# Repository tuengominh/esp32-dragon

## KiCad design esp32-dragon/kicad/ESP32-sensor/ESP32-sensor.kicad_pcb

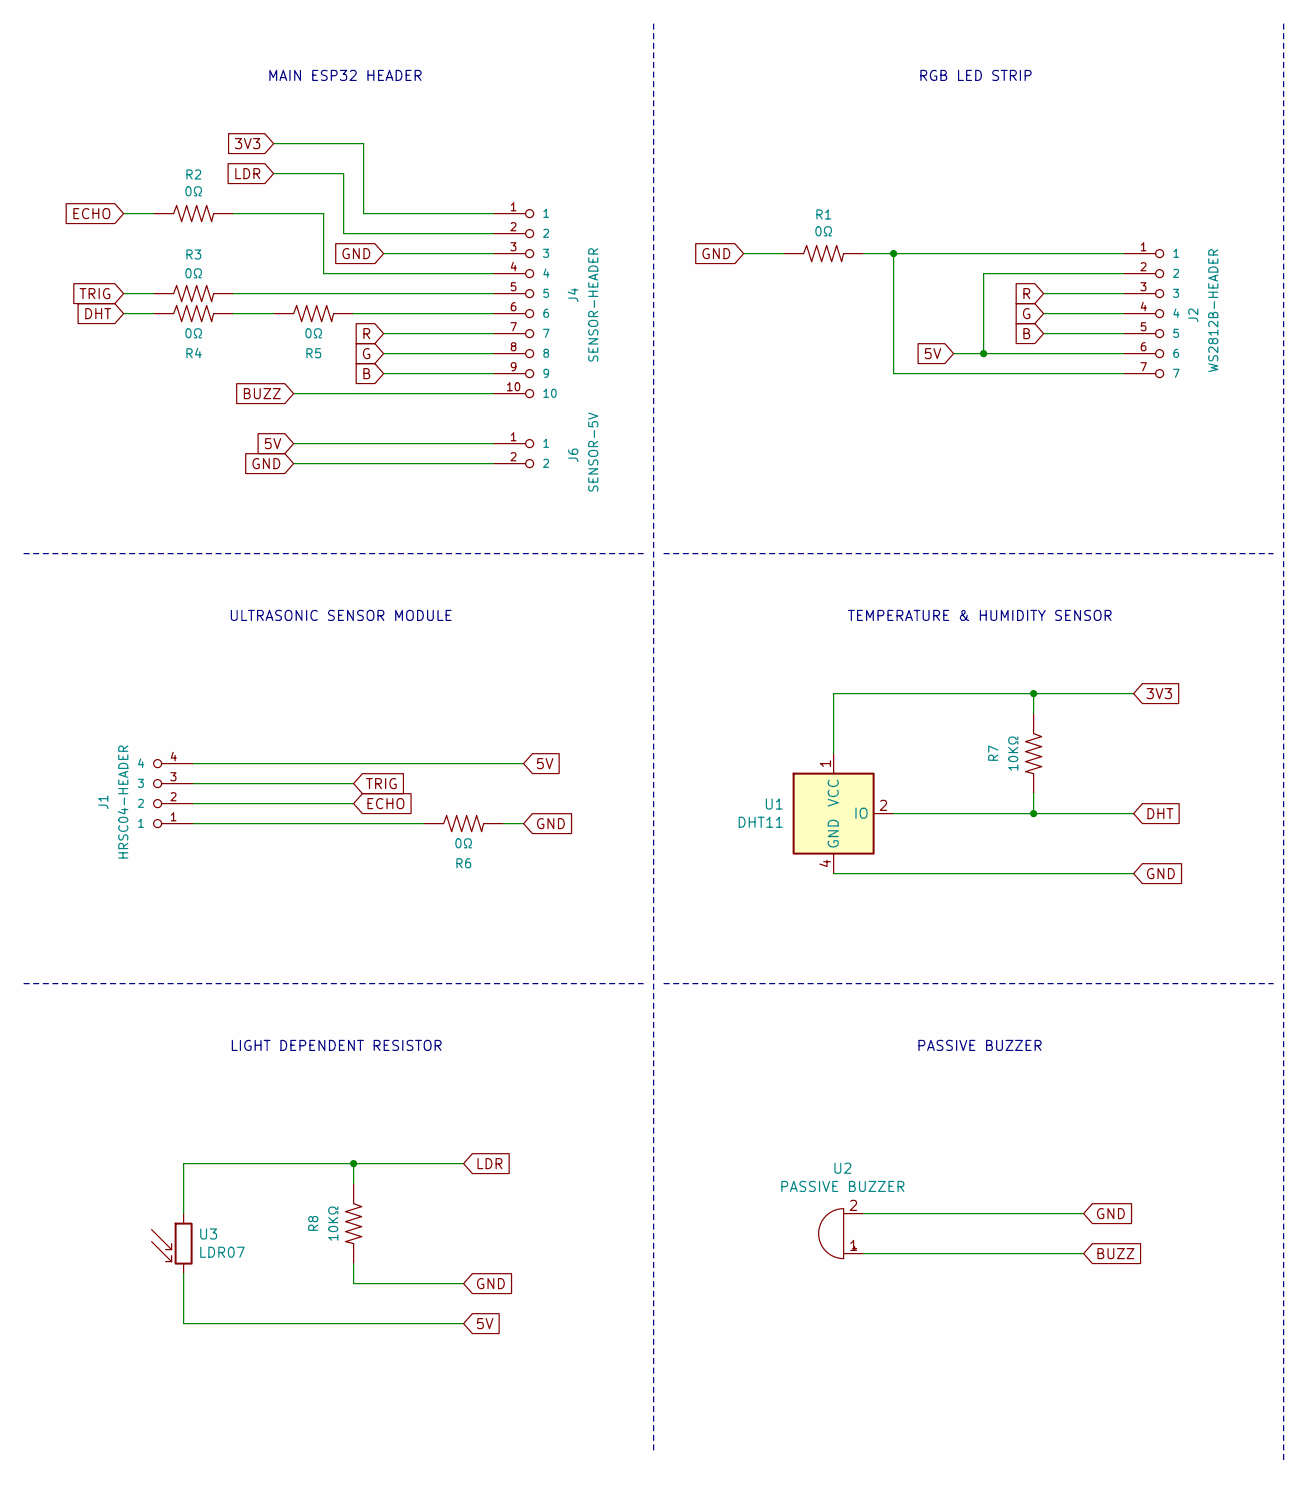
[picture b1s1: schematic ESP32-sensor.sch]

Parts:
J1: HRSC04-HEADER; fab-1X04
J2: WS2812B-HEADER; fab-1X07
J4: SENSOR-HEADER; fab-1X10
J6: SENSOR-5V; fab-1X02
R1, R2, R3, R4, R5, R6: 0Ω; fab-R1206FAB
R7, R8: 10KΩ; fab-R1206FAB
U1: DHT11; Aosong_DHT11_5.5x12.0_P2.54mm
U2: PASSIVE BUZZER; Buzzer_12x9.5RM7.6
U3: LDR07; R_LDR_5.1x4.3mm_P3.4mm_Vertical

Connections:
3V3: J4.1, R7.1, U1.1 (VCC)
5V: J1.4, J2.2, J2.6, J6.1, U3.2
B: J2.5, J4.9
BUZZ: J4.10, U2.1 (-)
DHT: R4.1, R7.2, U1.2 (IO)
ECHO: J1.2, R2.1
G: J2.4, J4.8
GND: J4.3, J6.2, R1.1, R6.2, R8.2, U1.4 (GND), U2.2 (+)
LDR: J4.2, R8.1, U3.1
unnamed: J1.1, R6.1
unnamed: J2.1, J2.7, R1.2
unnamed: J4.4, R2.2
unnamed: J4.5, R3.2
unnamed: J4.6, R5.2
unnamed: R4.2, R5.1
R: J2.3, J4.7
TRIG: J1.3, R3.1

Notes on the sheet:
MAIN ESP32 HEADER
RGB LED STRIP
ULTRASONIC SENSOR MODULE
TEMPERATURE & HUMIDITY SENSOR
PASSIVE BUZZER
LIGHT DEPENDENT RESISTOR

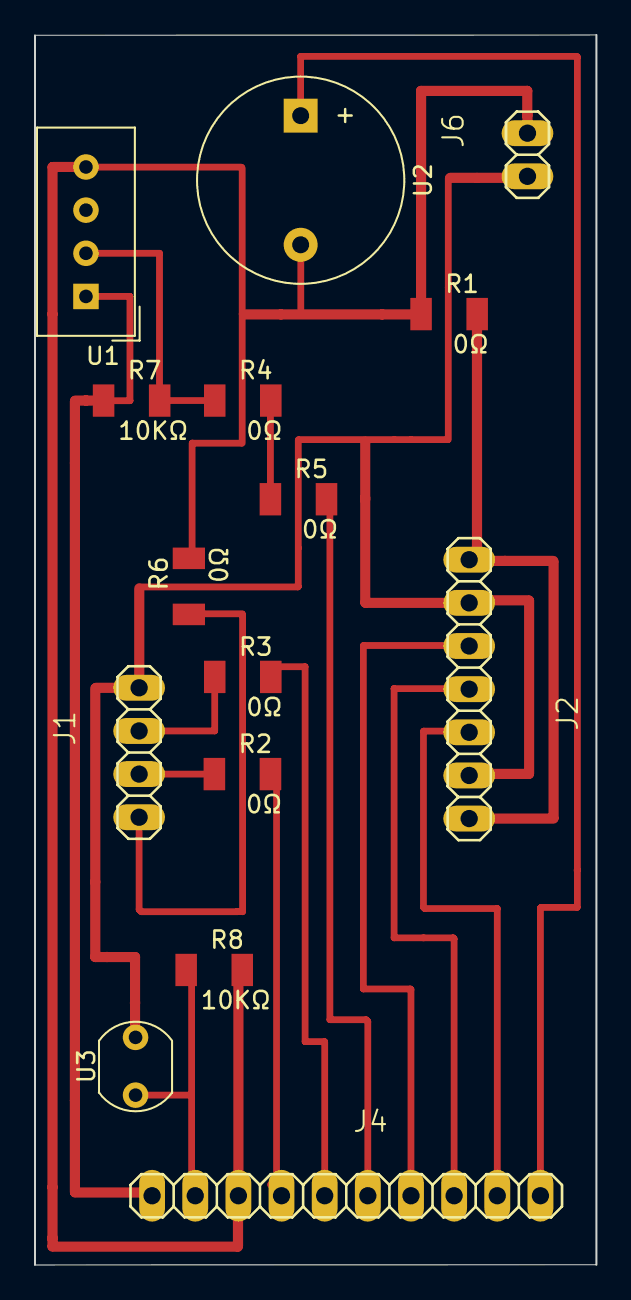
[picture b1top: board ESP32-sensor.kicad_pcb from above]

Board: 2 copper layers, 33.1 x 72.4 mm, 15 parts (0 on the bottom side), 17 nets.

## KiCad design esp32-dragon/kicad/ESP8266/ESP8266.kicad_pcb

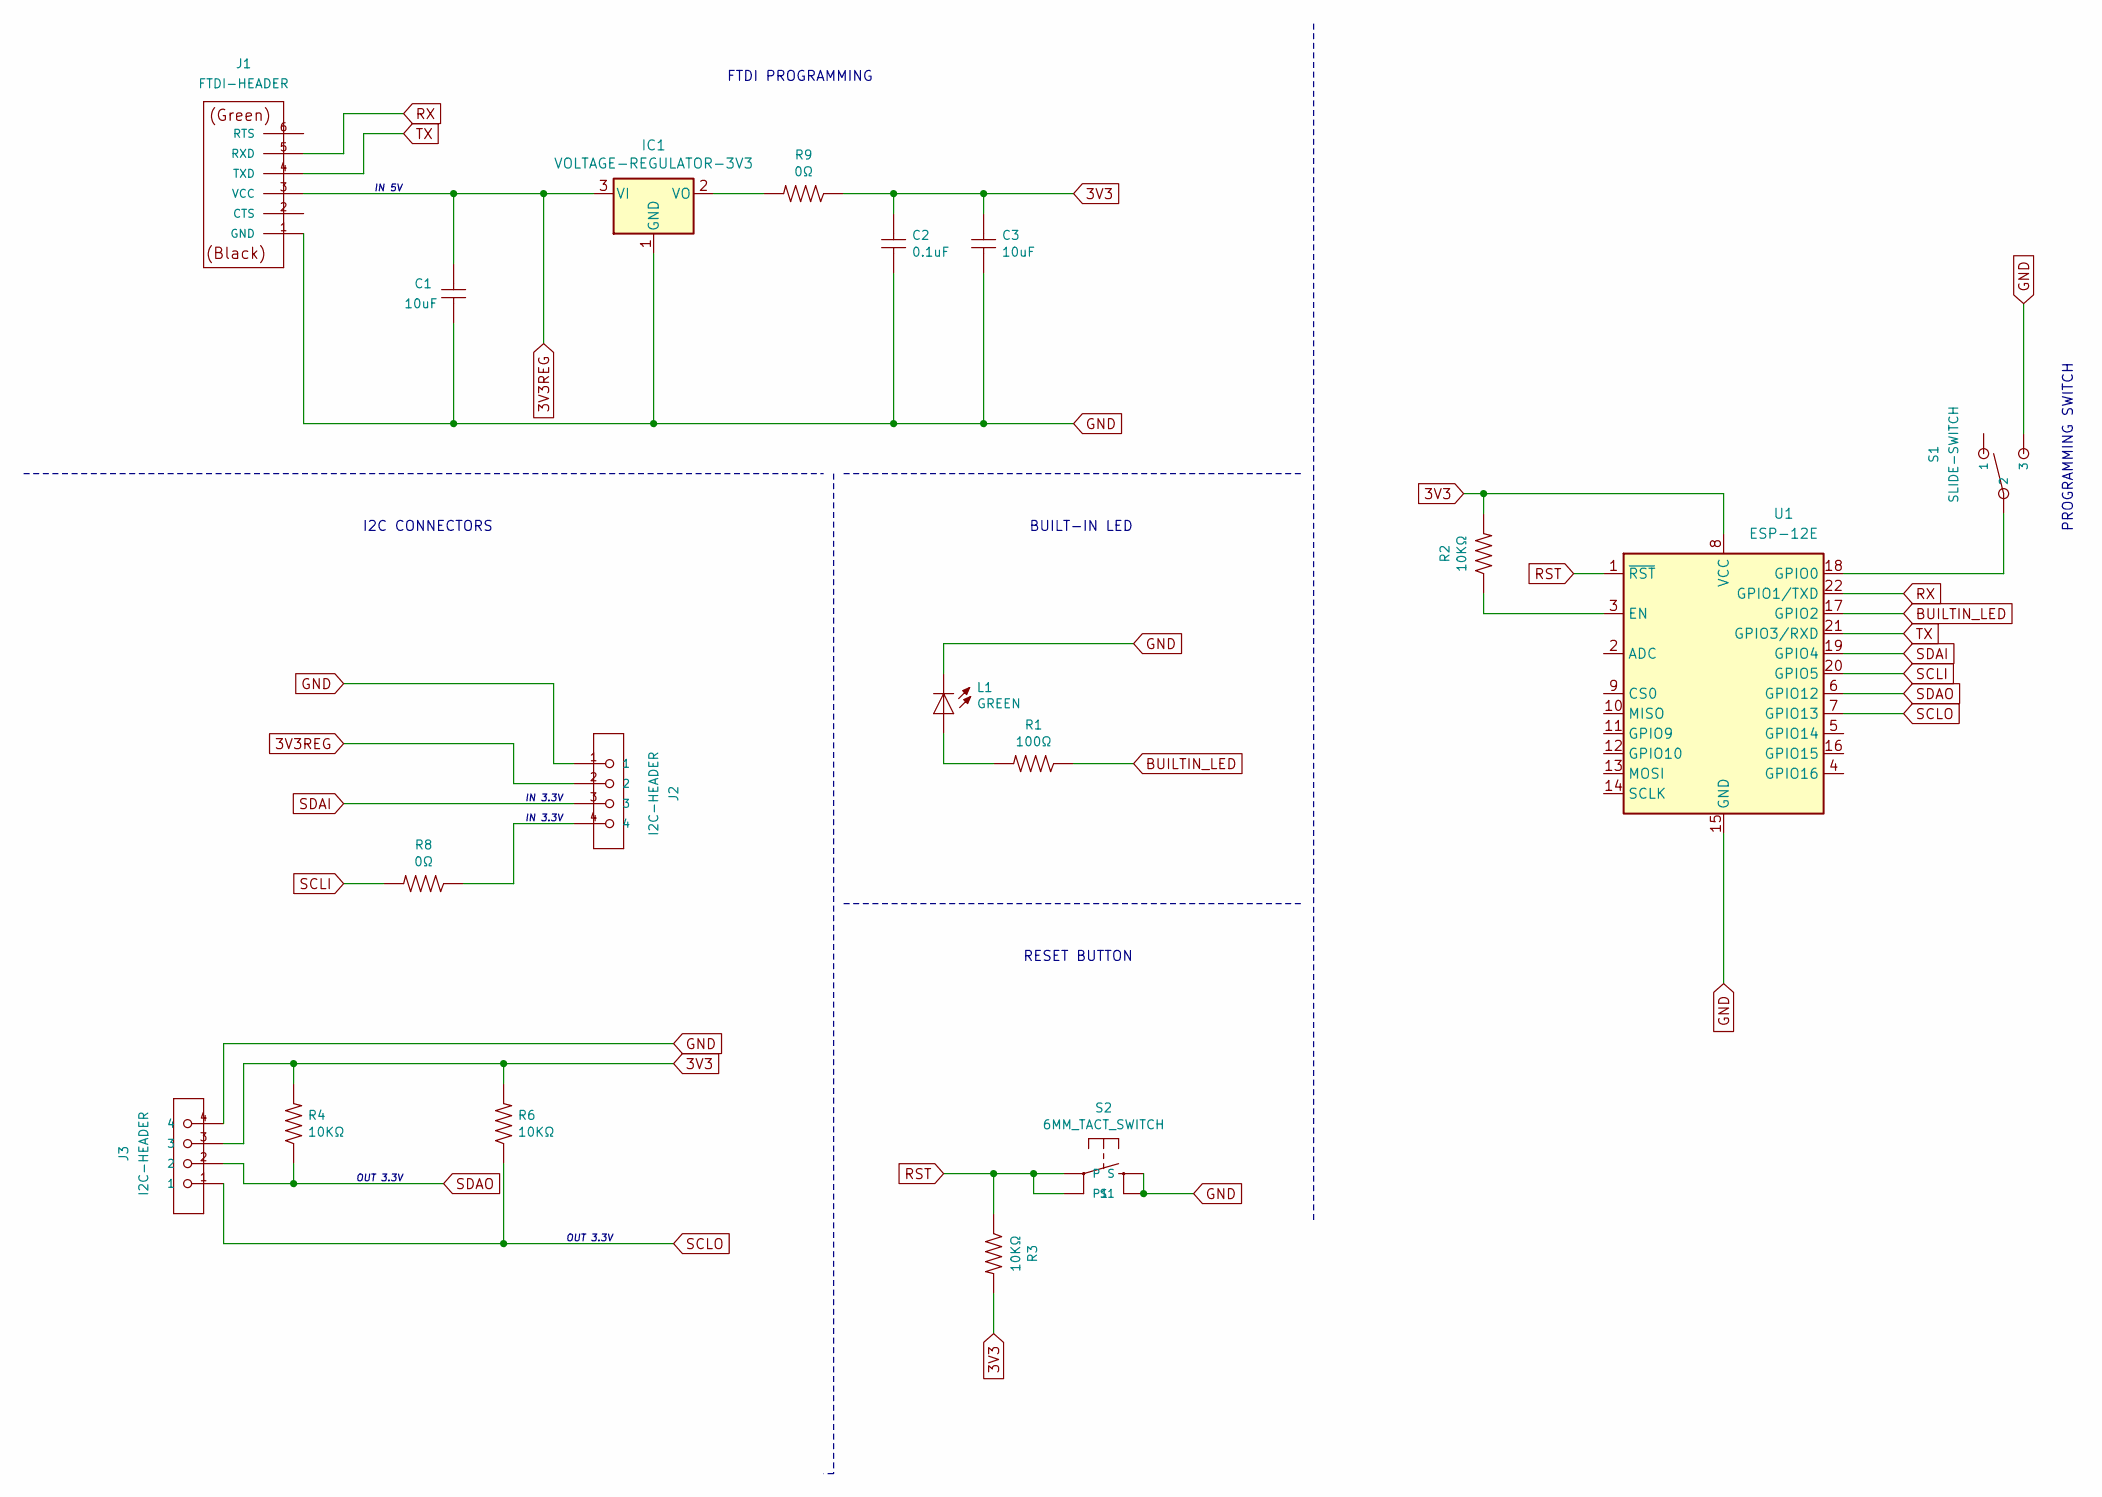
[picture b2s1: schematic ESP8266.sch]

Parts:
C1, C3: 10uF; fab-C1206FAB
C2: 0.1uF; fab-C1206FAB
IC1: VOLTAGE-REGULATOR-3V3; fab-SOT223
J1: FTDI-HEADER; fab-1X06SMD
J2, J3: I2C-HEADER; fab-1X04SMD
L1: GREEN; fab-LED1206FAB
R1: 100Ω; fab-R1206FAB
R2, R3, R4, R6: 10KΩ; fab-R1206FAB
R8, R9: 0Ω; fab-R1206FAB
S1: SLIDE-SWITCH; fab-AYZ0102AGRLC
S2: 6MM_TACT_SWITCH; fab-6MM_SWITCH
U1: ESP-12E

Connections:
3V3: C2.1, C3.1, J3.3, R2.2, R3.2, R4.2, R6.2, R9.1, U1.8 (VCC)
3V3REG: C1.1, IC1.3 (VI), J1.3 (VCC), J2.2
BUILTIN_LED: R1.1, U1.17 (GPIO2)
GND: C1.2, C2.2, C3.2, IC1.1 (GND), J1.1 (GND), J2.1, J3.4, L1.2 (C), S1.3, S2.3 (S), S2.4 (S1), U1.15 (GND)
unnamed: IC1.2 (VO), R9.2
unnamed: J2.4, R8.1
unnamed: L1.1 (A), R1.2
unnamed: R2.1, U1.3 (EN)
unnamed: S1.2, U1.18 (GPIO0)
RST: R3.1, S2.1, S2.2 (P1), U1.1 (~RST)
RX: J1.5 (RXD), U1.22 (GPIO1/TXD)
SCLI: R8.2, U1.20 (GPIO5)
SCLO: J3.1, R6.1, U1.7 (GPIO13)
SDAI: J2.3, U1.19 (GPIO4)
SDAO: J3.2, R4.1, U1.6 (GPIO12)
TX: J1.4 (TXD), U1.21 (GPIO3/RXD)

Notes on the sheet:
FTDI PROGRAMMING
IN 5V
RESET BUTTON
BUILT-IN LED
OUT 3.3V
I2C CONNECTORS
PROGRAMMING SWITCH
IN 3.3V

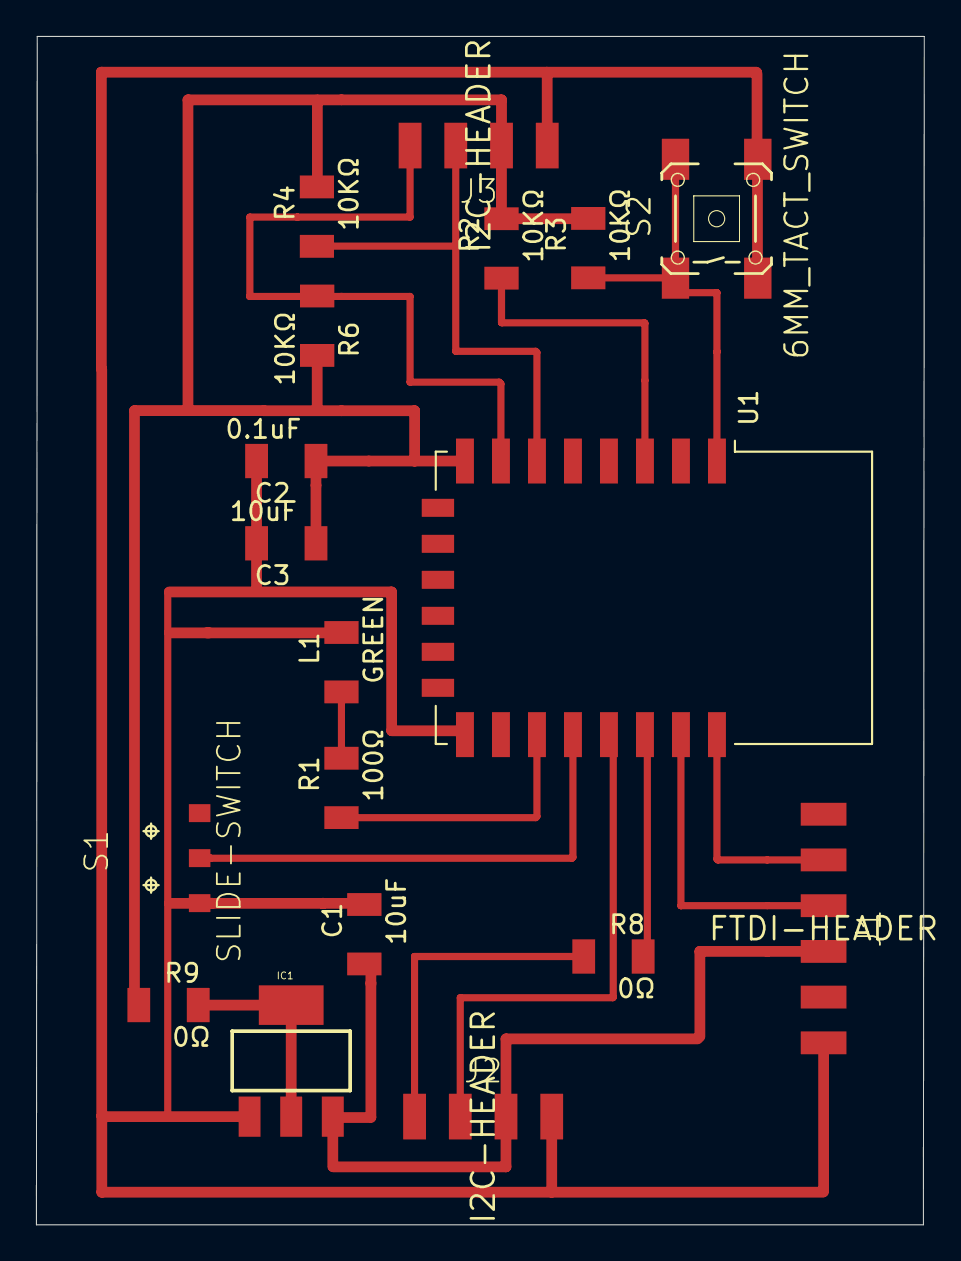
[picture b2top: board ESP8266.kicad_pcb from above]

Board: 2 copper layers, 49.3 x 66.0 mm, 18 parts (0 on the bottom side), 16 nets.

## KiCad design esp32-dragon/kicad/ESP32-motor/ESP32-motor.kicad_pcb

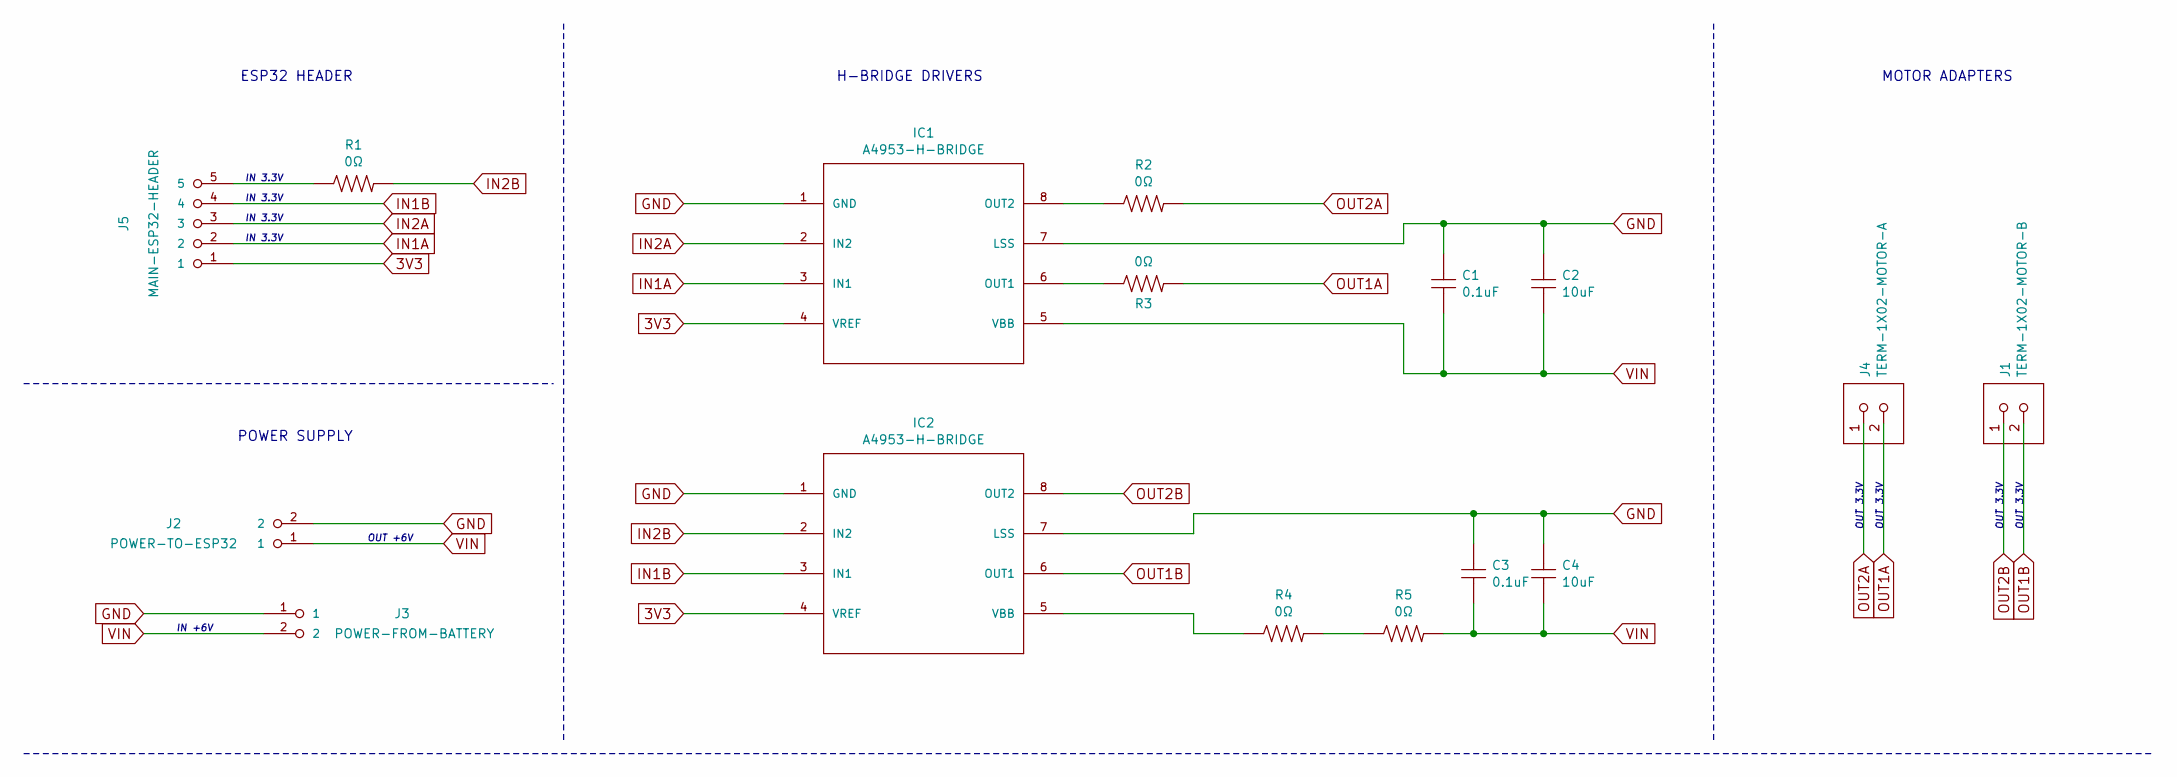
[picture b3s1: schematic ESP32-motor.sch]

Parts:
C1, C3: 0.1uF; fab-C1206FAB
C2, C4: 10uF; fab-C1206FAB
IC1, IC2: A4953-H-BRIDGE; fab-SOIC8
J1: TERM-1X02-MOTOR-B; fab-ED555DS-2DS
J2: POWER-TO-ESP32; fab-1X02
J3: POWER-FROM-BATTERY; HW2-SMD-2.0-90D
J4: TERM-1X02-MOTOR-A; fab-ED555DS-2DS
J5: MAIN-ESP32-HEADER; fab-1X05
R1, R2, R3, R4, R5: 0Ω; fab-R1206FAB

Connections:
3V3: IC1.4 (VREF), IC2.4 (VREF), J5.1
GND: C1.2, C2.2, C3.2, C4.2, IC1.1 (GND), IC1.7 (LSS), IC2.1 (GND), IC2.7 (LSS), J2.2, J3.1
IN1A: IC1.3 (IN1), J5.2
IN1B: IC2.3 (IN1), J5.4
IN2A: IC1.2 (IN2), J5.3
IN2B: IC2.2 (IN2), R1.2
unnamed: IC1.6 (OUT1), R3.1
unnamed: IC1.8 (OUT2), R2.1
unnamed: IC2.5 (VBB), R4.1
unnamed: J5.5, R1.1
unnamed: R4.2, R5.1
OUT1A: J4.2, R3.2
OUT1B: IC2.6 (OUT1), J1.2
OUT2A: J4.1, R2.2
OUT2B: IC2.8 (OUT2), J1.1
VIN: C1.1, C2.1, C3.1, C4.1, IC1.5 (VBB), J2.1, J3.2, R5.2

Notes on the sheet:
ESP32 HEADER
POWER SUPPLY
H-BRIDGE DRIVERS
MOTOR ADAPTERS
OUT +6V
IN +6V
IN 3.3V
OUT 3.3V

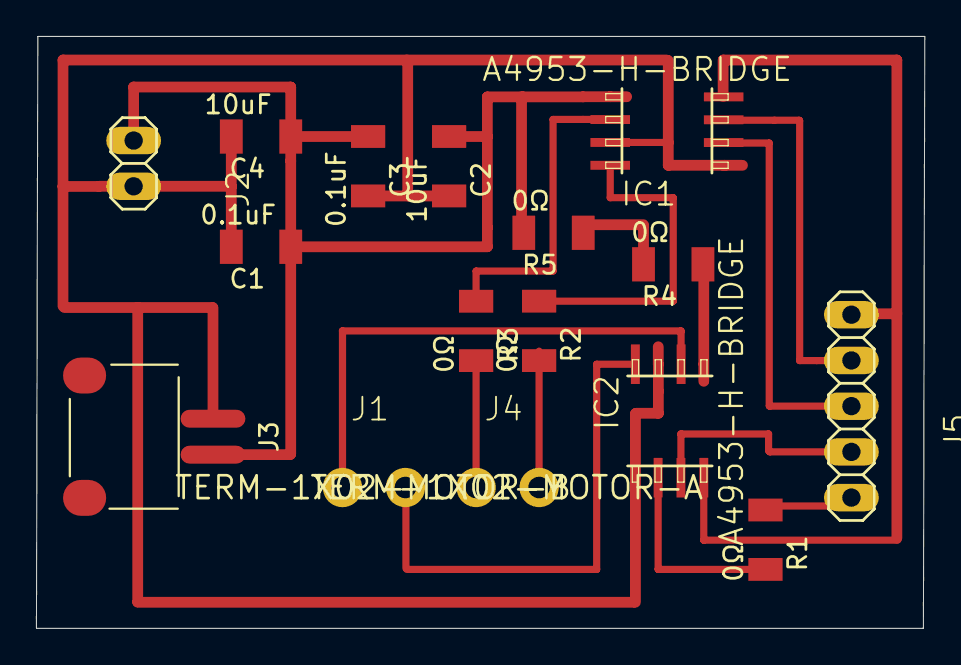
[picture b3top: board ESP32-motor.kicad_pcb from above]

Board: 2 copper layers, 49.4 x 32.9 mm, 16 parts (0 on the bottom side), 16 nets.

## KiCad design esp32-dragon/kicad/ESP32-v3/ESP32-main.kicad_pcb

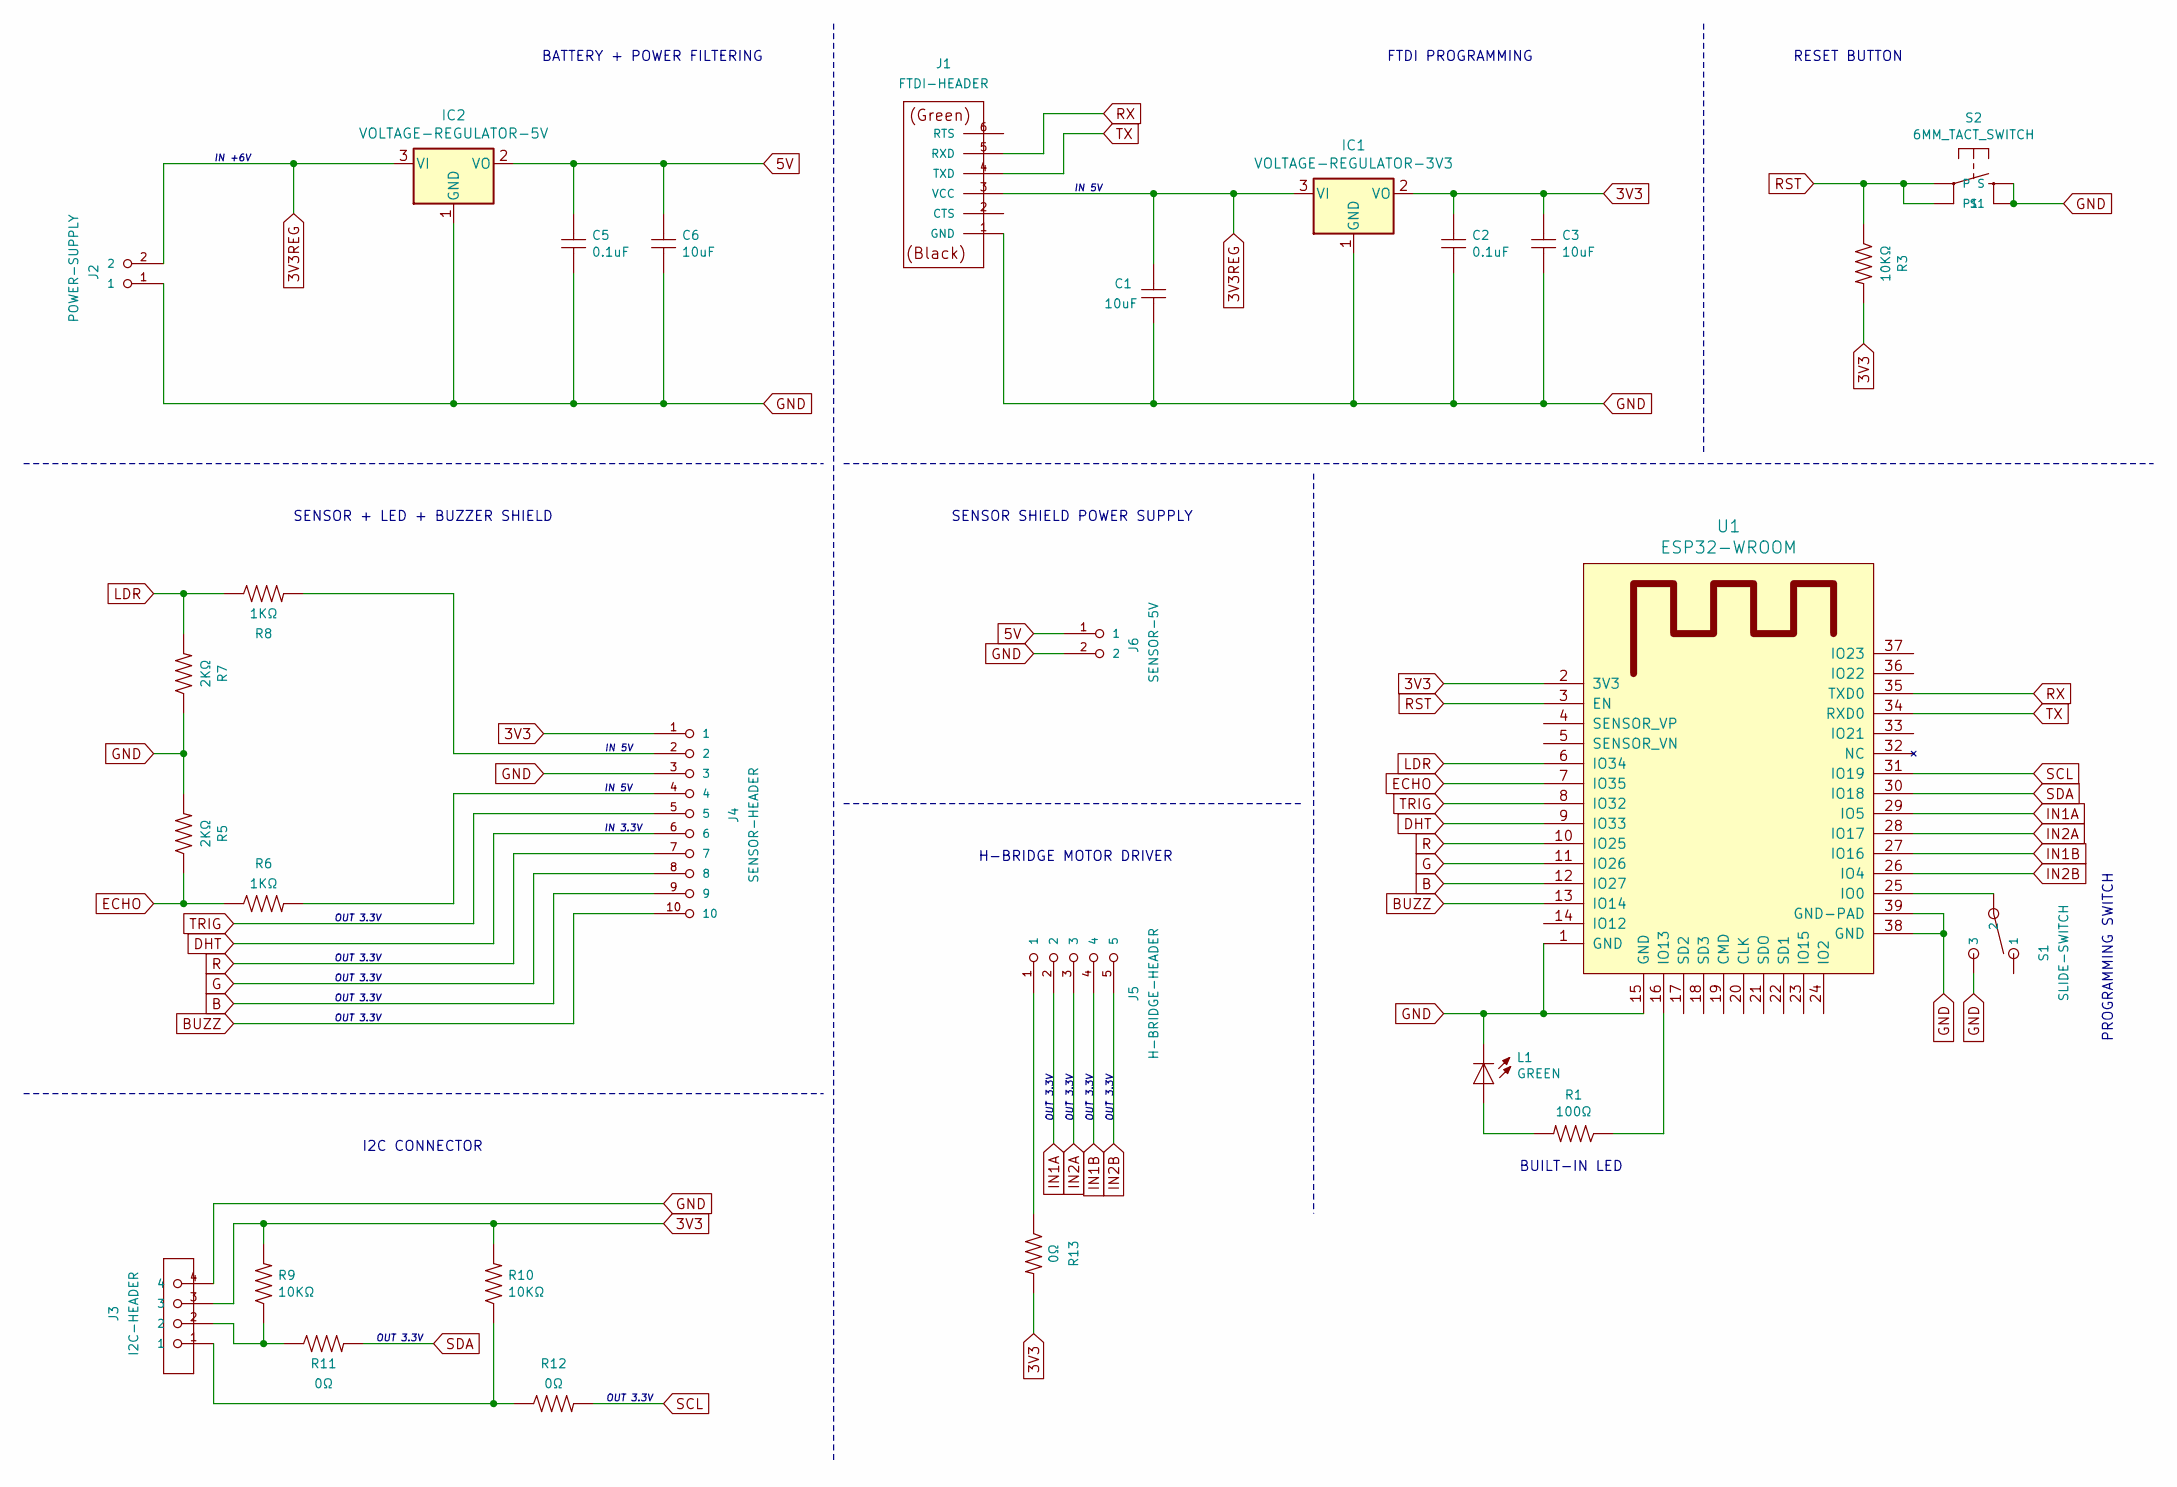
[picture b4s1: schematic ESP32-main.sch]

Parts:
C1, C3, C6: 10uF; fab-C1206FAB
C2, C5: 0.1uF; fab-C1206FAB
IC1: VOLTAGE-REGULATOR-3V3; fab-SOT223
IC2: VOLTAGE-REGULATOR-5V; fab-SOT223
J1: FTDI-HEADER; fab-1X06SMD
J2: POWER-SUPPLY; fab-1X02
J3: I2C-HEADER; fab-1X04SMD
J4: SENSOR-HEADER; fab-1X10
J5: H-BRIDGE-HEADER; fab-1X05
J6: SENSOR-5V; fab-1X02
L1: GREEN; fab-LED1206FAB
R1: 100Ω; fab-R1206FAB
R3, R9, R10: 10KΩ; fab-R1206FAB
R5, R7: 2KΩ; fab-R1206FAB
R6, R8: 1KΩ; fab-R1206FAB
R11, R12, R13: 0Ω; fab-R1206FAB
S1: SLIDE-SWITCH; fab-AYZ0102AGRLC
S2: 6MM_TACT_SWITCH; fab-6MM_SWITCH
U1: ESP32-WROOM; ESP32-WROOM_FAB

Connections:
3V3: C2.1, C3.1, IC1.2 (VO), J3.3, J4.1, R3.2, R9.2, R10.2, R13.2, U1.2 (3V3)
3V3REG: C1.1, IC1.3 (VI), IC2.3 (VI), J1.3 (VCC), J2.2
5V: C5.1, C6.1, IC2.2 (VO), J6.1
B: J4.9, U1.12 (IO27)
BUZZ: J4.10, U1.13 (IO14)
DHT: J4.6, U1.9 (IO33)
ECHO: R5.1, R6.1, U1.7 (IO35)
G: J4.8, U1.11 (IO26)
GND: C1.2, C2.2, C3.2, C5.2, C6.2, IC1.1 (GND), IC2.1 (GND), J1.1 (GND), J2.1, J3.4, J4.3, J6.2, L1.2 (C), R5.2, R7.1, S1.3, S2.3 (S), S2.4 (S1), U1.1 (GND), U1.15 (GND), U1.38 (GND), U1.39 (GND-PAD)
IN1A: J5.2, U1.29 (IO5)
IN1B: J5.4, U1.27 (IO16)
IN2A: J5.3, U1.28 (IO17)
IN2B: J5.5, U1.26 (IO4)
LDR: R7.2, R8.1, U1.6 (IO34)
unnamed: J3.1, R10.1, R12.1
unnamed: J3.2, R9.1, R11.1
unnamed: J4.2, R8.2
unnamed: J4.4, R6.2
unnamed: J5.1, R13.1
unnamed: L1.1 (A), R1.2
unnamed: R1.1, U1.16 (IO13)
unnamed: S1.2, U1.25 (IO0)
R: J4.7, U1.10 (IO25)
RST: R3.1, S2.1, S2.2 (P1), U1.3 (EN)
RX: J1.5 (RXD), U1.35 (TXD0)
SCL: R12.2, U1.31 (IO19)
SDA: R11.2, U1.30 (IO18)
TRIG: J4.5, U1.8 (IO32)
TX: J1.4 (TXD), U1.34 (RXD0)

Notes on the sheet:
FTDI PROGRAMMING
IN 5V
BATTERY + POWER FILTERING
RESET BUTTON
I2C CONNECTOR
PROGRAMMING SWITCH
BUILT-IN LED
H-BRIDGE MOTOR DRIVER
OUT 3.3V
IN 3.3V
SENSOR + LED + BUZZER SHIELD
SENSOR SHIELD POWER SUPPLY
IN +6V

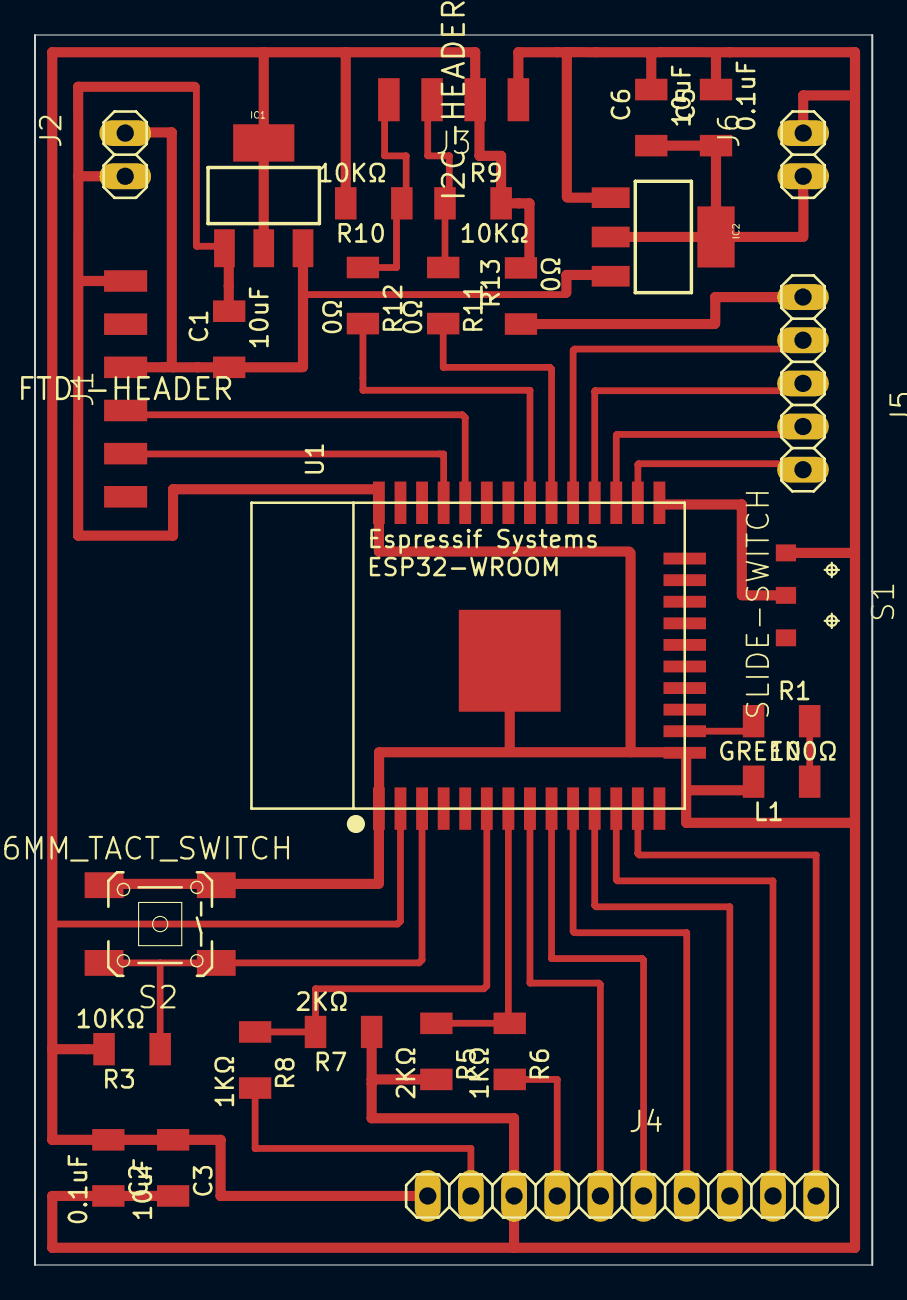
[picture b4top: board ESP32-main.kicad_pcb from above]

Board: 2 copper layers, 49.3 x 72.4 mm, 28 parts (0 on the bottom side), 29 nets.

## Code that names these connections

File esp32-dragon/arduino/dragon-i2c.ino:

#include <DHT.h>
#include <NewPing.h>
#include <Adafruit_NeoPixel.h>
#include <Wire.h>
#include <stdio.h>
#include <string.h>

#define BUILTIN_LED 13 
#define TRIGGER_PIN 32
#define ECHO_PIN 35
#define DHT_PIN 33
#define LDR_PIN 34
#define BUZZ_PIN 14
#define RGB_PIN 26
#define MOTORA_PIN1 4
#define MOTORA_PIN2 16 
#define MOTORB_PIN1 17 
#define MOTORB_PIN2 5 

int ldrValue;
float tempValue;
float humValue;
float distance;

#define DHTTYPE DHT11
NewPing sonar(TRIGGER_PIN, ECHO_PIN, 200); 
DHT dht(DHT_PIN, DHTTYPE);

#define LED_COUNT 10
Adafruit_NeoPixel strip(LED_COUNT, RGB_PIN, NEO_GRB + NEO_KHZ800);

String inputId = "";
String outputId = "";
String logicId = "";
String data = "BUZZ,IF,DARK";
//const byte I2C_MASTER_ADDR = 0x20;
//const byte I2C_SLAVE_ADDR = 0x20;

void setup() {
  pinMode(BUILTIN_LED, OUTPUT);
  pinMode(BUZZ_PIN, OUTPUT);
  pinMode(MOTORA_PIN1, OUTPUT);
  pinMode(MOTORA_PIN2, OUTPUT);
  pinMode(MOTORB_PIN1, OUTPUT);
  pinMode(MOTORB_PIN2, OUTPUT); 

  Serial.begin(115200);
  //Wire.begin(I2C_MASTER_ADDR);
  //Wire.begin(I2C_SDA, I2C_SCL);
  
  dht.begin();
  strip.begin();           
  strip.show();             
  strip.setBrightness(150); 
}

void loop() {
  delay(100);
  //Wire.onReceive(receiveEvent);
  splitIds();
  
  if (logicId == "IF") { // if input then output 
    if (inputId == "LIGHT") {
        if (readLDR() >= 60) {
          executeOutput(outputId);
        }
      } else if (inputId == "DARK") {
        if (readLDR() < 60) {
          executeOutput(outputId);
        }
      } else if (inputId == "HOT") {
        if (readTemp() >= 30) {
          executeOutput(outputId);
        }
      } else if (inputId == "COLD") {
        if (readTemp() <= 15) {
          executeOutput(outputId);
        }
      } else if (inputId == "PROX") {
        if (readDistance() <= 8) {
          executeOutput(outputId);
        }
      } else {
        Serial.println("Error input!");
        blinkLED();
      } 
  }
  else if (logicId == "UNTIL") { // until input keep output 
     if (inputId == "LIGHT") {
        while (readLDR() < 60) {
          executeOutput(outputId);
        }
      } else if (inputId == "DARK") {
        while (readLDR() > 60) {
          executeOutput(outputId);
        }
      } else if (inputId == "HOT") {
        while (readTemp() < 30) {
          executeOutput(outputId);
        }
      } else if (inputId == "COLD") {
        while (readTemp() > 15) {
          executeOutput(outputId);
        }
      } else if (inputId == "PROX") {
        while (readDistance() > 8) {
          executeOutput(outputId);
        }
      } else {
        Serial.println("Error input!");
        blinkLED();
      } 
  }
  else {
    Serial.println("Error logic!");
    blinkLED(); 
  }
}

void executeOutput(String id) {
  if (id == "FIRE") {
    blinkRed();
  } else if (id == "FLASH") {
    blinkWhite();
  } else if (id == "BUZZ") {
    buzz();
  } else if (id == "FOR") {
    moveForward();
    stopDC();
  } else if (id == "BACK") {
    moveBackward();  
    stopDC();
  } else {
    Serial.println("Error output!");
    blinkLED(); 
  } 
}

// check IDs
/*void receiveEvent(int byteCount) {
  Wire.requestFrom(I2C_SLAVE_ADDR, 20);
  while (Wire.available())
  {
     data += (char)Wire.read();
     Serial.println(data);
     data = "";
  }
}*/ 

void splitIds() {
  int commaIndex = data.indexOf(',');
  int secondCommaIndex = data.indexOf(',', commaIndex + 1);
  outputId = data.substring(0, commaIndex);
  logicId = data.substring(commaIndex + 1, secondCommaIndex);
  inputId = data.substring(secondCommaIndex + 1);
  Serial.println(inputId + " - " + logicId + " - " + outputId);
}

// debugging
void blinkLED() {
  digitalWrite(BUILTIN_LED, LOW);   
  delay(500);                     
  digitalWrite(BUILTIN_LED, HIGH);  
  delay(500);
}

// read sensors
int readLDR() {
  delay(500);  
  ldrValue = analogRead(LDR_PIN);
  Serial.print(ldrValue); 
  Serial.println(" \n"); 
  return ldrValue;
}

int readTemp() {
  delay(500);  
  tempValue = dht.readTemperature();
  Serial.print(tempValue);
  Serial.print("°C");
  Serial.println(" \n"); 
  return tempValue;  
}

int readHum() {
  delay(500);  
  humValue = dht.readHumidity();  
  Serial.print(humValue);
  Serial.println(" \n");
  return humValue;
}

int readDistance() {
  delay(500);
  distance = sonar.ping_cm();
  Serial.print(distance); 
  Serial.print("cm");
  Serial.println(" \n"); 
  return distance; 
}

// control buzzer
void buzz() {
  Serial.println("Buzz!");
  digitalWrite(BUZZ_PIN, HIGH);   
  delay(500);                       
  digitalWrite(BUZZ_PIN, LOW);    
  delay(500);
}

// control LED strip
void blinkRed() {
  Serial.println("Fire!");
  colorWipe(strip.Color(255, 0, 0), 500);
}

void blinkWhite() {
  Serial.println("Flash!");
  colorWipe(strip.Color(255, 255, 255), 500);
}

void colorWipe(uint32_t color, int wait) {
  for(int i = 0; i < strip.numPixels(); i++) { 
    strip.setPixelColor(i, color);         
    strip.show();                          
    delay(wait);                          
  }
}

// control DC motor
void stopDC() {
  Serial.println("Motors stop!"); 
  digitalWrite(MOTORA_PIN1, LOW);
  digitalWrite(MOTORA_PIN2, LOW);
  digitalWrite(MOTORB_PIN1, LOW);
  digitalWrite(MOTORB_PIN2, LOW);
  delay(1000);
}

void moveForward() {
  Serial.println("Motors move forward!");
  digitalWrite(MOTORA_PIN1, LOW);
  digitalWrite(MOTORA_PIN2, HIGH); 
  digitalWrite(MOTORB_PIN1, LOW);
  digitalWrite(MOTORB_PIN2, HIGH); 
  delay(5000);
}

void moveBackward() {
  Serial.println("Motors move backward!");
  digitalWrite(MOTORA_PIN1, HIGH);
  digitalWrite(MOTORA_PIN2, LOW); 
  digitalWrite(MOTORB_PIN1, HIGH);
  digitalWrite(MOTORB_PIN2, LOW); 
  delay(5000);
}

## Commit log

2020-12-08 Add paho-mqtt
2023-03-01 clean up
